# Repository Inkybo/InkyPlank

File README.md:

# InkyPlank

This is a plank style keyboard based off the RP2040 with MX switches

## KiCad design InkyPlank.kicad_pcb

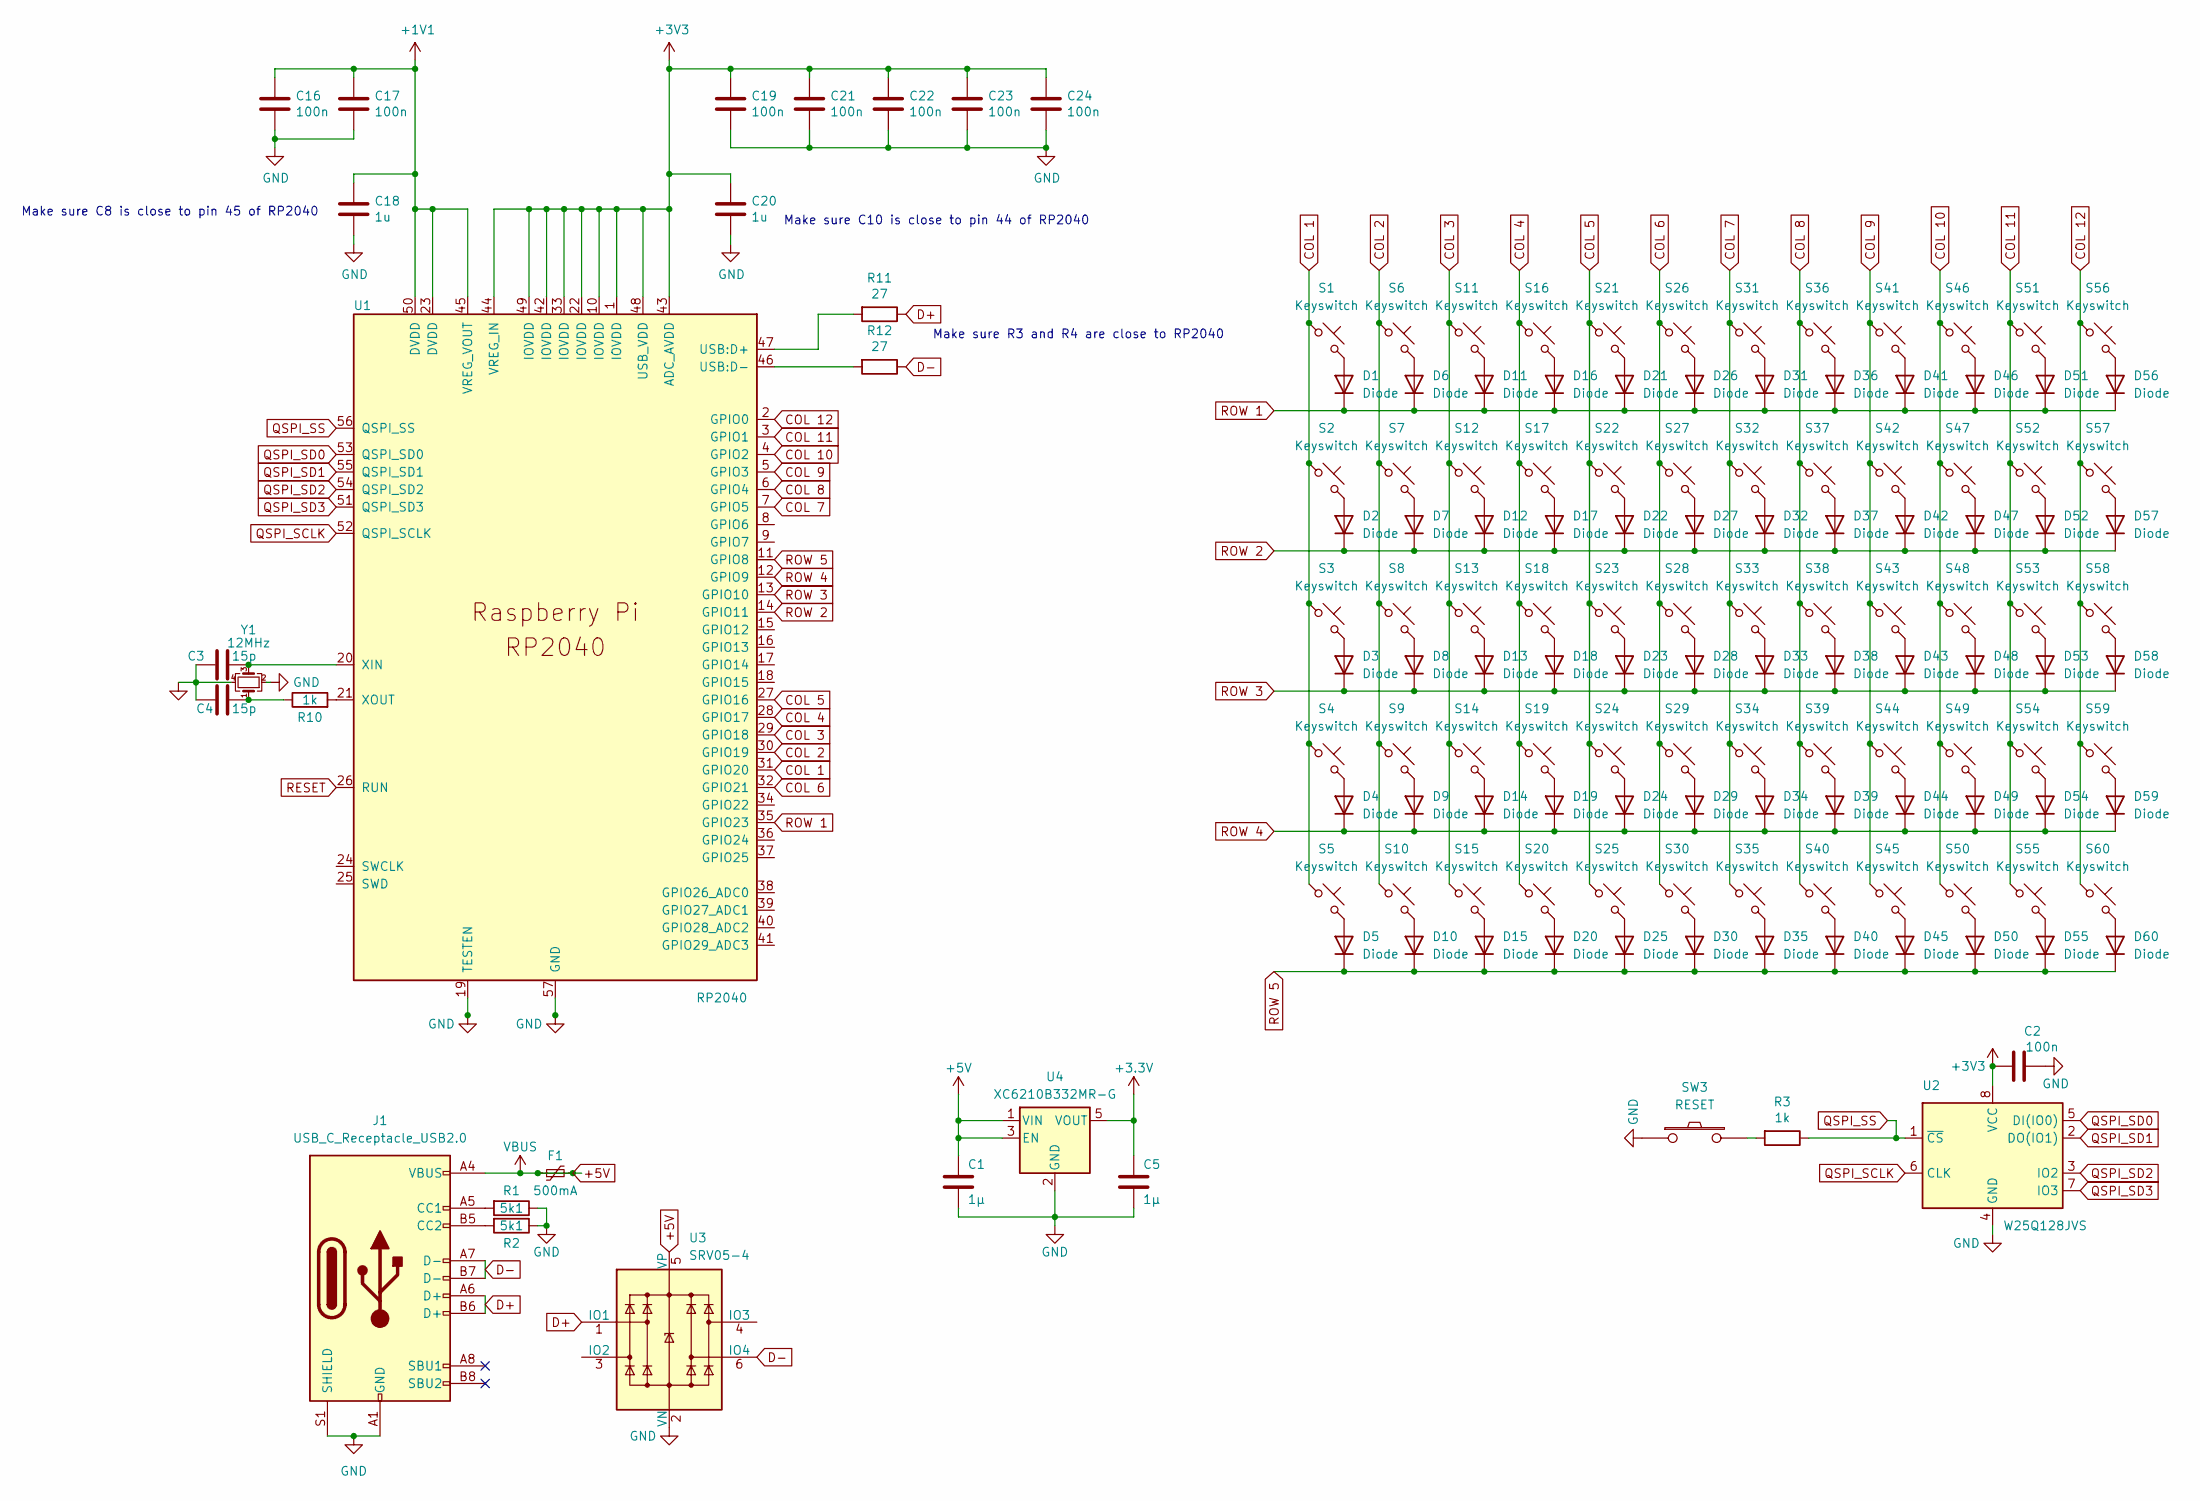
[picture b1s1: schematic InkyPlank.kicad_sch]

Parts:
C1, C5: 1µ; C_0402_1005Metric; LCSC C19666
C2, C16, C17, C19, C21, C22, C23, C24: 100n; C_0402_1005Metric; LCSC C49678
C3, C4: 15p; C_0402_1005Metric; MPN 0402CG150J500NT; LCSC C1548
C18, C20: 1u; C_0402_1005Metric; LCSC C28323
D1, D2, D3, D4, D5, D6, D7, D8, D9, D10, D11, D12, D13, D14, D15, D16, D17, D18, D19, D20, D21, D22, D23, D24, D25, D26, D27, D28, D29, D30, D31, D32, D33, D34, D35, D36, D37, D38, D39, D40, D41, D42, D43, D44, D45, D46, D47, D48, D49, D50, D51, D52, D53, D54, D55, D56, D57, D58, D59, D60: Diode; D_SOD-123
F1: 500mA; Fuse_0603_1608Metric; MPN MF-FSMF050X-2; LCSC C210357
J1: USB_C_Receptacle_USB2.0; USB_C_Receptacle_HRO_TYPE-C-31-M-12
R1, R2: 5k1; R_0805_2012Metric
R3: 1k; R_0805_2012Metric; LCSC C115316
R10: 1k; R_0402_1005Metric; MPN 0402WGF1001TCE; LCSC C11702
R11, R12: 27; R_0805_2012Metric; LCSC C104170
S1, S2, S3, S4, S5, S6, S7, S8, S9, S10, S11, S12, S13, S14, S15, S16, S17, S18, S19, S20, S21, S22, S23, S24, S25, S26, S27, S28, S29, S30, S31, S32, S33, S34, S35, S36, S37, S38, S39, S40, S41, S42, S43, S44, S45, S46, S47, S48, S49, S50, S51, S52, S53, S54, S55, S56, S57, S58, S59, S60: Keyswitch; MX_PCB_1.00u
SW3: RESET; SW_SPST_TL3342; LCSC C318884
U1: RP2040; RP2040-QFN-56; LCSC C2040
U2: W25Q128JVS; SOIC-8_5.23x5.23mm_P1.27mm; LCSC C97521
U3: SRV05-4; SOT-23-6; LCSC C85364
U4: XC6210B332MR-G; SOT-23-5; LCSC C82942
Y1: 12MHz; Crystal_SMD_2520-4Pin_2.5x2.0mm; MPN 2TJ412000HYGBC; LCSC C2149204

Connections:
+1V1: C16.1, C17.1, C18.1, U1.23 (DVDD), U1.45 (VREG_VOUT), U1.50 (DVDD)
+5V: C1.1, F1.1, F1.2, J1.A4 (VBUS), J1.A9 (VBUS), J1.B4 (VBUS), J1.B9 (VBUS), U3.5 (VP), U4.1 (VIN), U4.3 (EN)
COL 1: S1.1, S2.1, S3.1, S4.1, S5.1, U1.31 (GPIO20)
COL 2: S6.1, S7.1, S8.1, S9.1, S10.1, U1.30 (GPIO19)
COL 3: S11.1, S12.1, S13.1, S14.1, S15.1, U1.29 (GPIO18)
COL 4: S16.1, S17.1, S18.1, S19.1, S20.1, U1.28 (GPIO17)
COL 5: S21.1, S22.1, S23.1, S24.1, S25.1, U1.27 (GPIO16)
COL 6: S26.1, S27.1, S28.1, S29.1, S30.1, U1.32 (GPIO21)
COL 7: S31.1, S32.1, S33.1, S34.1, S35.1, U1.7 (GPIO5)
COL 8: S36.1, S37.1, S38.1, S39.1, S40.1, U1.6 (GPIO4)
COL 9: S41.1, S42.1, S43.1, S44.1, S45.1, U1.5 (GPIO3)
COL 10: S46.1, S47.1, S48.1, S49.1, S50.1, U1.4 (GPIO2)
COL 11: S51.1, S52.1, S53.1, S54.1, S55.1, U1.3 (GPIO1)
COL 12: S56.1, S57.1, S58.1, S59.1, S60.1, U1.2 (GPIO0)
D+: J1.A6 (D+), J1.B6 (D+), R11.1, U3.1 (IO1)
D-: J1.A7 (D-), J1.B7 (D-), R12.1, U3.6 (IO4)
GND: C1.2, C2.2, C3.1, C4.1, C5.2, C16.2, C17.2, C18.2, C19.2, C20.2, C21.2, C22.2, C23.2, C24.2, J1.A1 (GND), J1.A12 (GND), J1.B1 (GND), J1.B12 (GND), J1.S1 (SHIELD), R1.1, R2.1, SW3.1, U1.19 (TESTEN), U1.57 (GND), U2.4 (GND), U3.2 (VN), U4.2 (GND), Y1.2, Y1.4
unnamed: C4.2, R10.1, Y1.1
unnamed: D1.2 (A), S1.2
unnamed: D2.2 (A), S2.2
unnamed: D3.2 (A), S3.2
unnamed: D4.2 (A), S4.2
unnamed: D5.2 (A), S5.2
unnamed: D6.2 (A), S6.2
unnamed: D7.2 (A), S7.2
unnamed: D8.2 (A), S8.2
unnamed: D9.2 (A), S9.2
unnamed: D10.2 (A), S10.2
unnamed: D11.2 (A), S11.2
unnamed: D12.2 (A), S12.2
unnamed: D13.2 (A), S13.2
unnamed: D14.2 (A), S14.2
unnamed: D15.2 (A), S15.2
unnamed: D16.2 (A), S16.2
unnamed: D17.2 (A), S17.2
unnamed: D18.2 (A), S18.2
unnamed: D19.2 (A), S19.2
unnamed: D20.2 (A), S20.2
unnamed: D21.2 (A), S21.2
unnamed: D22.2 (A), S22.2
unnamed: D23.2 (A), S23.2
unnamed: D24.2 (A), S24.2
unnamed: D25.2 (A), S25.2
unnamed: D26.2 (A), S26.2
unnamed: D27.2 (A), S27.2
unnamed: D28.2 (A), S28.2
unnamed: D29.2 (A), S29.2
unnamed: D30.2 (A), S30.2
unnamed: D31.2 (A), S31.2
unnamed: D32.2 (A), S32.2
unnamed: D33.2 (A), S33.2
unnamed: D34.2 (A), S34.2
unnamed: D35.2 (A), S35.2
unnamed: D36.2 (A), S36.2
unnamed: D37.2 (A), S37.2
unnamed: D38.2 (A), S38.2
unnamed: D39.2 (A), S39.2
unnamed: D40.2 (A), S40.2
unnamed: D41.2 (A), S41.2
unnamed: D42.2 (A), S42.2
unnamed: D43.2 (A), S43.2
unnamed: D44.2 (A), S44.2
unnamed: D45.2 (A), S45.2
unnamed: D46.2 (A), S46.2
unnamed: D47.2 (A), S47.2
unnamed: D48.2 (A), S48.2
unnamed: D49.2 (A), S49.2
unnamed: D50.2 (A), S50.2
unnamed: D51.2 (A), S51.2
unnamed: D52.2 (A), S52.2
unnamed: D53.2 (A), S53.2
unnamed: D54.2 (A), S54.2
unnamed: D55.2 (A), S55.2
unnamed: D56.2 (A), S56.2
unnamed: D57.2 (A), S57.2
unnamed: D58.2 (A), S58.2
unnamed: D59.2 (A), S59.2
unnamed: D60.2 (A), S60.2
unnamed: J1.A5 (CC1), R1.2
unnamed: J1.B5 (CC2), R2.2
unnamed: R3.2, SW3.2
unnamed: R11.2, U1.47 (USB:D+)
unnamed: R12.2, U1.46 (USB:D-)
unnamed: C3.2, U1.20 (XIN), Y1.3
unnamed: R10.2, U1.21 (XOUT)
QSPI_SCLK: U1.52 (QSPI_SCLK), U2.6 (CLK)
QSPI_SD0: U1.53 (QSPI_SD0), U2.5 (DI(IO0))
QSPI_SD1: U1.55 (QSPI_SD1), U2.2 (DO(IO1))
QSPI_SD2: U1.54 (QSPI_SD2), U2.3 (IO2)
QSPI_SD3: U1.51 (QSPI_SD3), U2.7 (IO3)
QSPI_SS: R3.1, U1.56 (QSPI_SS), U2.1 (~CS)
RESET: U1.26 (RUN)
ROW 1: D1.1 (K), D6.1 (K), D11.1 (K), D16.1 (K), D21.1 (K), D26.1 (K), D31.1 (K), D36.1 (K), D41.1 (K), D46.1 (K), D51.1 (K), D56.1 (K), U1.35 (GPIO23)
ROW 2: D2.1 (K), D7.1 (K), D12.1 (K), D17.1 (K), D22.1 (K), D27.1 (K), D32.1 (K), D37.1 (K), D42.1 (K), D47.1 (K), D52.1 (K), D57.1 (K), U1.14 (GPIO11)
ROW 3: D3.1 (K), D8.1 (K), D13.1 (K), D18.1 (K), D23.1 (K), D28.1 (K), D33.1 (K), D38.1 (K), D43.1 (K), D48.1 (K), D53.1 (K), D58.1 (K), U1.13 (GPIO10)
ROW 4: D4.1 (K), D9.1 (K), D14.1 (K), D19.1 (K), D24.1 (K), D29.1 (K), D34.1 (K), D39.1 (K), D44.1 (K), D49.1 (K), D54.1 (K), D59.1 (K), U1.12 (GPIO9)
ROW 5: D5.1 (K), D10.1 (K), D15.1 (K), D20.1 (K), D25.1 (K), D30.1 (K), D35.1 (K), D40.1 (K), D45.1 (K), D50.1 (K), D55.1 (K), D60.1 (K), U1.11 (GPIO8)

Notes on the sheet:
Make sure R3 and R4 are close to RP2040
Make sure C10 is close to pin 44 of RP2040
Make sure C8 is close to pin 45 of RP2040

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
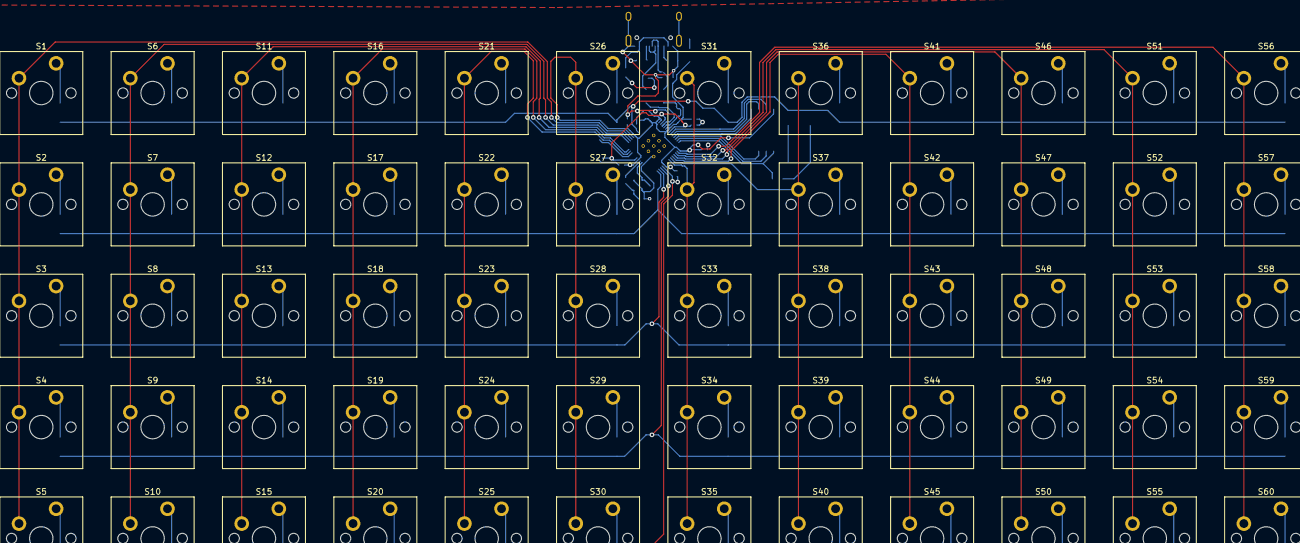
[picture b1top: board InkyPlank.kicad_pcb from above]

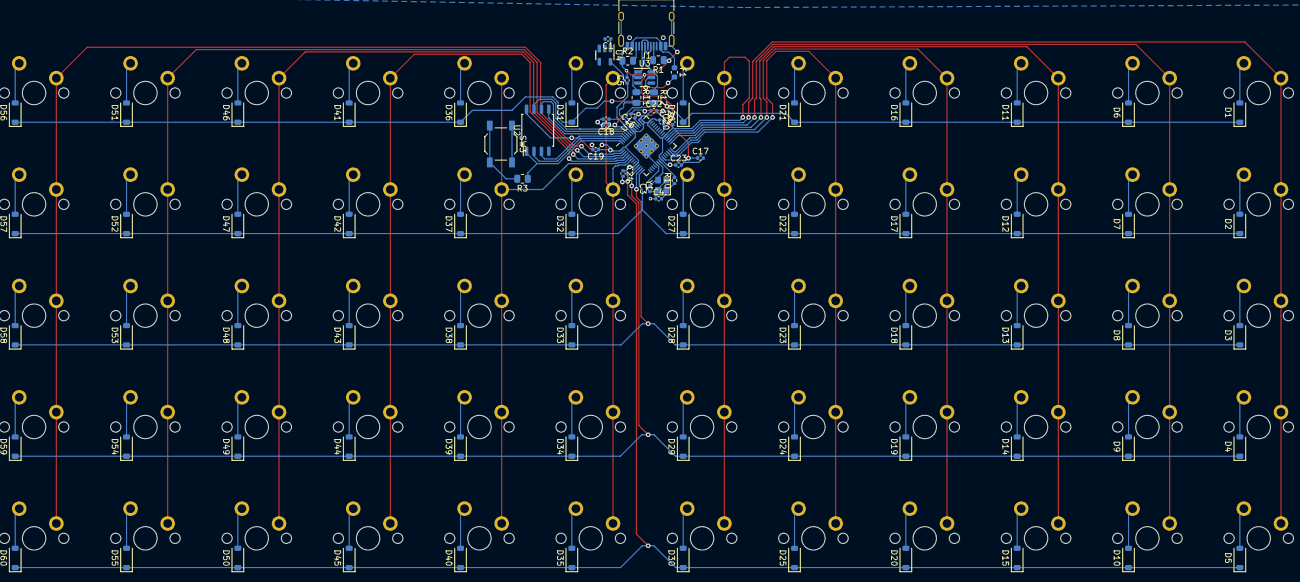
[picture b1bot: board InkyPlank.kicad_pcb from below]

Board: 2 copper layers, 148 parts (88 on the bottom side), 97 nets.

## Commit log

2023-10-22 first commit, from 🇩🇪️ with <3
2023-10-22 full commit from 🇩🇪️ with <3
